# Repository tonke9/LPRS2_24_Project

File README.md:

# LPRS2_2024

[Prj table](https://docs.google.com/spreadsheets/d/1Rkn6w4jnjtR-49NMRK07prfJrvV3ZWLn)

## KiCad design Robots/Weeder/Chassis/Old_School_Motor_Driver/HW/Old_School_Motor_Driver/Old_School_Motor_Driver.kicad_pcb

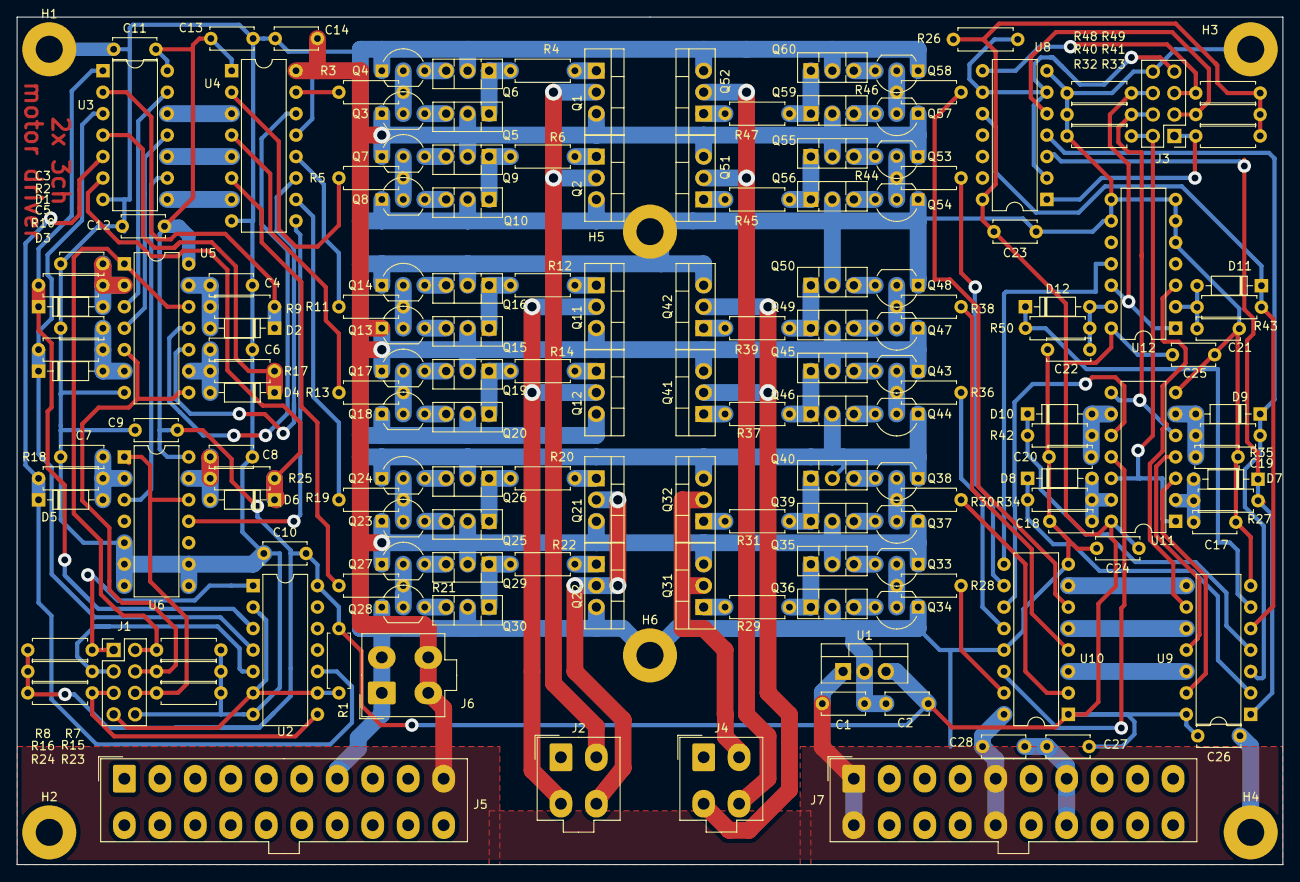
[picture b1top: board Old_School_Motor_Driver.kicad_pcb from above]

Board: 2 copper layers, 149.9 x 100.3 mm, 172 parts (0 on the bottom side), 137 nets.

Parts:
C1, C2, C9, C10, C11, C12, C13, C14, C23, C24, C25, C26, C27, C28: 0u1; C_Disc_D5.0mm_W2.5mm_P5.00mm
C3, C4, C5, C6, C7, C8, C17, C18, C19, C20, C21, C22: 47p; C_Disc_D5.0mm_W2.5mm_P5.00mm
D1, D2, D3, D4, D5, D6, D7, D8, D9, D10, D11, D12: 1N4148; D_DO-35_SOD27_P7.62mm_Horizontal
H1, H2, H3, H4: Board legs mounting hole; MountingHole_3.2mm_M3_Pad
H5, H6: Heatsink mounting hole; MountingHole_3.2mm_M3_Pad
J1, J3: 2x8 2.54mm male; PinHeader_2x04_P2.54mm_Vertical
J2, J4, J6: 2x2 4.2mm Molex ATX male header vertical; Molex_Mini-Fit_Jr_5566-04A_2x02_P4.20mm_Vertical
J5, J7: 2x10 4.2mm Molex ATX male header vertical; Molex_Mini-Fit_Jr_5566-20A_2x10_P4.20mm_Vertical
Q1, Q11, Q21, Q31, Q41, Q51: IRF9Z34N; TO-220-3_Vertical
Q2, Q12, Q22, Q32, Q42, Q52: IRFZ44N; TO-220-3_Vertical
Q3, Q7, Q13, Q17, Q23, Q27, Q33, Q37, Q43, Q47, Q53, Q57: BC547; TO-92_Inline_Wide
Q4, Q8, Q14, Q18, Q24, Q28, Q34, Q38, Q44, Q48, Q54, Q58: BC557; TO-92_Inline_Wide
Q5, Q9, Q15, Q19, Q25, Q29, Q35, Q39, Q45, Q49, Q55, Q59: BD139; TO-126-3_Vertical
Q6, Q10, Q16, Q20, Q26, Q30, Q36, Q40, Q46, Q50, Q56, Q60: BD140; TO-126-3_Vertical
R1, R7, R8, R15, R16, R23, R24, R26, R32, R33, R40, R41, R48, R49: 1M; R_Axial_DIN0207_L6.3mm_D2.5mm_P7.62mm_Horizontal
R2, R9, R10, R17, R18, R25, R27, R34, R35, R42, R43, R50: 22k; R_Axial_DIN0207_L6.3mm_D2.5mm_P7.62mm_Horizontal
R3, R5, R11, R13, R19, R21, R28, R30, R36, R38, R44, R46: 12k; R_Axial_DIN0207_L6.3mm_D2.5mm_P7.62mm_Horizontal
R4, R6, R12, R14, R20, R22, R29, R31, R37, R39, R45, R47: 10 0W6; R_Axial_DIN0207_L6.3mm_D2.5mm_P7.62mm_Horizontal
U1: L7805; TO-220-3_Vertical
U2, U8: 4070; DIP-14_W7.62mm
U3, U9: 4069; DIP-14_W7.62mm
U4, U10: 4504; DIP-16_W7.62mm
U5, U6, U11, U12: 4093; DIP-14_W7.62mm

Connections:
+5V: C2.2, C9.2, C10.2, C11.2, C12.2, C13.2, C23.2, C24.2, C25.2, C26.2, C27.2, R1.1, R8.1, R16.1, R24.1, R26.1, R33.1, R41.1, R49.1, U1.3, U2.14, U3.14, U4.1, U5.14, U6.14, U8.14, U9.14, U10.1, U11.14, U12.14
+12V: C1.2, C14.1, C28.1, J5.10, J6.3, J6.4, J7.1, J7.5, J7.11, J7.15, Q1.3, Q3.1, Q5.2, Q7.1, Q9.2, Q11.3, Q13.1, Q15.2, Q17.1, Q19.2, Q21.3, Q23.1, Q25.2, Q27.1, Q29.2, Q31.3, Q33.1, Q35.2, Q37.1, Q39.2, Q41.3, Q43.1, Q45.2, Q47.1, Q49.2, Q51.3, Q53.1, Q55.2, Q57.1, Q59.2, U1.1, U4.16, U10.16
/side0/EN[0]: J1.2, R7.2, U5.1, U5.12
/side0/EN[1]: J1.4, R15.2, U5.5, U5.8
/side0/EN[2]: J1.6, R23.2, U6.1, U6.12
/side0/IN[0]: J1.1, R8.2, U2.1
/side0/IN[1]: J1.3, R16.2, U2.5
/side0/IN[2]: J1.5, R24.2, U2.8
/side0/OUT[0]: J2.2, Q1.2, Q2.2
/side0/OUT[1]: J2.3, Q11.2, Q12.2
/side0/OUT[2]: J2.4, Q21.2, Q22.2
/side0/PWM: J1.7, R1.2, U2.2, U2.6, U2.9
/side0/channel0/DT_L: U3.13, U5.3
/side0/channel0/DT_U: U4.14, U5.11
/side0/channel0/D_L: R5.2, U4.2
/side0/channel0/D_U: R3.2, U4.15
/side0/channel0/N_DT_L: U3.12, U4.3
/side0/channel0/N_SIG: D1.1, R2.2, U2.3, U3.1
/side0/channel0/SIG: D2.1, R9.2, U3.2
/side0/channel0/dt0.0/drc/DRC: C4.1, D2.2, R9.1, U5.13
/side0/channel0/dt0.1/drc/DRC: C3.1, D1.2, R2.1, U5.2
/side0/channel0/mosfets_with_driver/G_L: Q2.1, R6.1
/side0/channel0/mosfets_with_driver/G_U: Q1.1, R4.1
/side0/channel1/DT_L: U3.11, U5.4
/side0/channel1/DT_U: U4.11, U5.10
/side0/channel1/D_L: R13.2, U4.4
/side0/channel1/D_U: R11.2, U4.12
/side0/channel1/N_DT_L: U3.10, U4.5
/side0/channel1/N_SIG: D3.1, R10.2, U2.4, U3.3
/side0/channel1/SIG: D4.1, R17.2, U3.4
/side0/channel1/dt1.0/drc/DRC: C6.1, D4.2, R17.1, U5.9
/side0/channel1/dt1.1/drc/DRC: C5.1, D3.2, R10.1, U5.6
/side0/channel1/mosfets_with_driver/G_L: Q12.1, R14.1
/side0/channel1/mosfets_with_driver/G_U: Q11.1, R12.1
/side0/channel2/DT_L: U3.9, U6.3
/side0/channel2/DT_U: U4.9, U6.11
/side0/channel2/D_L: R21.2, U4.6
/side0/channel2/D_U: R19.2, U4.10
/side0/channel2/N_DT_L: U3.8, U4.7
/side0/channel2/N_SIG: D5.1, R18.2, U2.10, U3.5
/side0/channel2/SIG: D6.1, R25.2, U3.6
/side0/channel2/dt2.0/drc/DRC: C8.1, D6.2, R25.1, U6.13
/side0/channel2/dt2.1/drc/DRC: C7.1, D5.2, R18.1, U6.2
/side0/channel2/mosfets_with_driver/G_L: Q22.1, R22.1
/side0/channel2/mosfets_with_driver/G_U: Q21.1, R20.1
/side1/EN[0]: J3.2, R32.2, U11.1, U11.12
/side1/EN[1]: J3.4, R40.2, U11.5, U11.8
/side1/EN[2]: J3.6, R48.2, U12.1, U12.12
/side1/IN[0]: J3.1, R33.2, U8.1
/side1/IN[1]: J3.3, R41.2, U8.5
/side1/IN[2]: J3.5, R49.2, U8.8
/side1/OUT[0]: J4.2, Q31.2, Q32.2
/side1/OUT[1]: J4.3, Q41.2, Q42.2
/side1/OUT[2]: J4.4, Q51.2, Q52.2
/side1/PWM: J3.7, R26.2, U8.2, U8.6, U8.9
/side1/channel0/DT_L: U9.13, U11.3
/side1/channel0/DT_U: U10.14, U11.11
/side1/channel0/D_L: R30.2, U10.2
/side1/channel0/D_U: R28.2, U10.15
/side1/channel0/N_DT_L: U9.12, U10.3
/side1/channel0/N_SIG: D7.1, R27.2, U8.3, U9.1
/side1/channel0/SIG: D8.1, R34.2, U9.2
/side1/channel0/dt0.0/drc/DRC: C18.1, D8.2, R34.1, U11.13
/side1/channel0/dt0.1/drc/DRC: C17.1, D7.2, R27.1, U11.2
/side1/channel0/mosfets_with_driver/G_L: Q32.1, R31.1
/side1/channel0/mosfets_with_driver/G_U: Q31.1, R29.1
/side1/channel1/DT_L: U9.11, U11.4
/side1/channel1/DT_U: U10.11, U11.10
/side1/channel1/D_L: R38.2, U10.4
/side1/channel1/D_U: R36.2, U10.12
/side1/channel1/N_DT_L: U9.10, U10.5
/side1/channel1/N_SIG: D9.1, R35.2, U8.4, U9.3
/side1/channel1/SIG: D10.1, R42.2, U9.4
/side1/channel1/dt1.0/drc/DRC: C20.1, D10.2, R42.1, U11.9
/side1/channel1/dt1.1/drc/DRC: C19.1, D9.2, R35.1, U11.6
/side1/channel1/mosfets_with_driver/G_L: Q42.1, R39.1
/side1/channel1/mosfets_with_driver/G_U: Q41.1, R37.1
/side1/channel2/DT_L: U9.9, U12.3
/side1/channel2/DT_U: U10.9, U12.11
/side1/channel2/D_L: R46.2, U10.6
/side1/channel2/D_U: R44.2, U10.10
/side1/channel2/N_DT_L: U9.8, U10.7
/side1/channel2/N_SIG: D11.1, R43.2, U8.10, U9.5
/side1/channel2/SIG: D12.1, R50.2, U9.6
/side1/channel2/dt2.0/drc/DRC: C22.1, D12.2, R50.1, U12.13
/side1/channel2/dt2.1/drc/DRC: C21.1, D11.2, R43.1, U12.2
/side1/channel2/mosfets_with_driver/G_L: Q52.1, R47.1
/side1/channel2/mosfets_with_driver/G_U: Q51.1, R45.1
GND: C1.1, C2.1, C3.2, C4.2, C5.2, C6.2, C7.2, C8.2, C9.1, C10.1, C11.1, C12.1, C13.1, C14.2, C17.2, C18.2, C19.2, C20.2, C21.2, C22.2, C23.1, C24.1, C25.1, C26.1, C27.1, C28.2, H1.1, H2.1, H3.1, H4.1, H5.1, H6.1, J1.8, J2.1, J3.8, J4.1, J5.3, J5.5, J5.7, J5.13, J5.14, J5.15, J5.16, J5.17, J6.1, J6.2, J7.3, J7.7, J7.13, J7.17, Q2.3, Q4.1, Q6.2, Q8.1, Q10.2, Q12.3, Q14.1, Q16.2, Q18.1, Q20.2, Q22.3, Q24.1, Q26.2, Q28.1, Q30.2, Q32.3, Q34.1, Q36.2, Q38.1, Q40.2, Q42.3, Q44.1, Q46.2, Q48.1, Q50.2, Q52.3, Q54.1, Q56.2, Q58.1, Q60.2, R7.1, R15.1, R23.1, R32.1, R40.1, R48.1, U1.2, U2.7, U3.7, U4.8, U4.13, U5.7, U6.5, U6.6, U6.7, U6.8, U6.9, U8.7, U9.7, U10.8, U10.13, U11.7, U12.5, U12.6, U12.7, U12.8, U12.9
unnamed: Q3.2, Q4.2, R3.1
unnamed: Q3.3, Q5.3
unnamed: Q4.3, Q6.3
unnamed: Q5.1, Q6.1, R4.2
unnamed: Q7.2, Q8.2, R5.1
unnamed: Q7.3, Q9.3
unnamed: Q9.1, Q10.1, R6.2
unnamed: Q8.3, Q10.3
unnamed: Q13.2, Q14.2, R11.1
unnamed: Q13.3, Q15.3
unnamed: Q14.3, Q16.3
unnamed: Q15.1, Q16.1, R12.2
unnamed: Q17.2, Q18.2, R13.1
unnamed: Q17.3, Q19.3
unnamed: Q18.3, Q20.3
unnamed: Q19.1, Q20.1, R14.2
unnamed: Q23.2, Q24.2, R19.1
unnamed: Q23.3, Q25.3
unnamed: Q24.3, Q26.3
unnamed: Q25.1, Q26.1, R20.2
unnamed: Q27.2, Q28.2, R21.1
unnamed: Q27.3, Q29.3
unnamed: Q28.3, Q30.3
unnamed: Q29.1, Q30.1, R22.2
unnamed: Q33.2, Q34.2, R28.1
unnamed: Q33.3, Q35.3
unnamed: Q34.3, Q36.3
unnamed: Q35.1, Q36.1, R29.2
unnamed: Q37.2, Q38.2, R30.1
unnamed: Q37.3, Q39.3
unnamed: Q38.3, Q40.3
unnamed: Q39.1, Q40.1, R31.2
unnamed: Q43.2, Q44.2, R36.1
unnamed: Q43.3, Q45.3
unnamed: Q44.3, Q46.3
unnamed: Q45.1, Q46.1, R37.2
unnamed: Q47.2, Q48.2, R38.1
unnamed: Q47.3, Q49.3
unnamed: Q48.3, Q50.3
unnamed: Q49.1, Q50.1, R39.2
unnamed: Q53.2, Q54.2, R44.1
unnamed: Q53.3, Q55.3
unnamed: Q54.3, Q56.3
unnamed: Q55.1, Q56.1, R45.2
unnamed: Q57.2, Q58.2, R46.1
unnamed: Q57.3, Q59.3
unnamed: Q58.3, Q60.3
unnamed: Q59.1, Q60.1, R47.2

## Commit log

2024-04-02 Usual stuff.
2024-04-02 OBD2
2024-04-03 Adding.
2024-04-03 For chassis.
2024-05-20 FW for Weeled Chassis team.
2024-05-20 For NOx crew.
2024-05-20 Analizator gasa
2024-05-27 Promena SW i HW
2024-05-31 UPDATE 31.05.
2024-06-11 11.06.2024.
2024-06-13 nova doc
2024-06-18 18.06.2024
2024-06-19 Tables edited
2024-06-19 New table
2024-06-20 Final version
